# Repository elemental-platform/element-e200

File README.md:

# element-e200
Wireless motion sensor based on RFM69 radio

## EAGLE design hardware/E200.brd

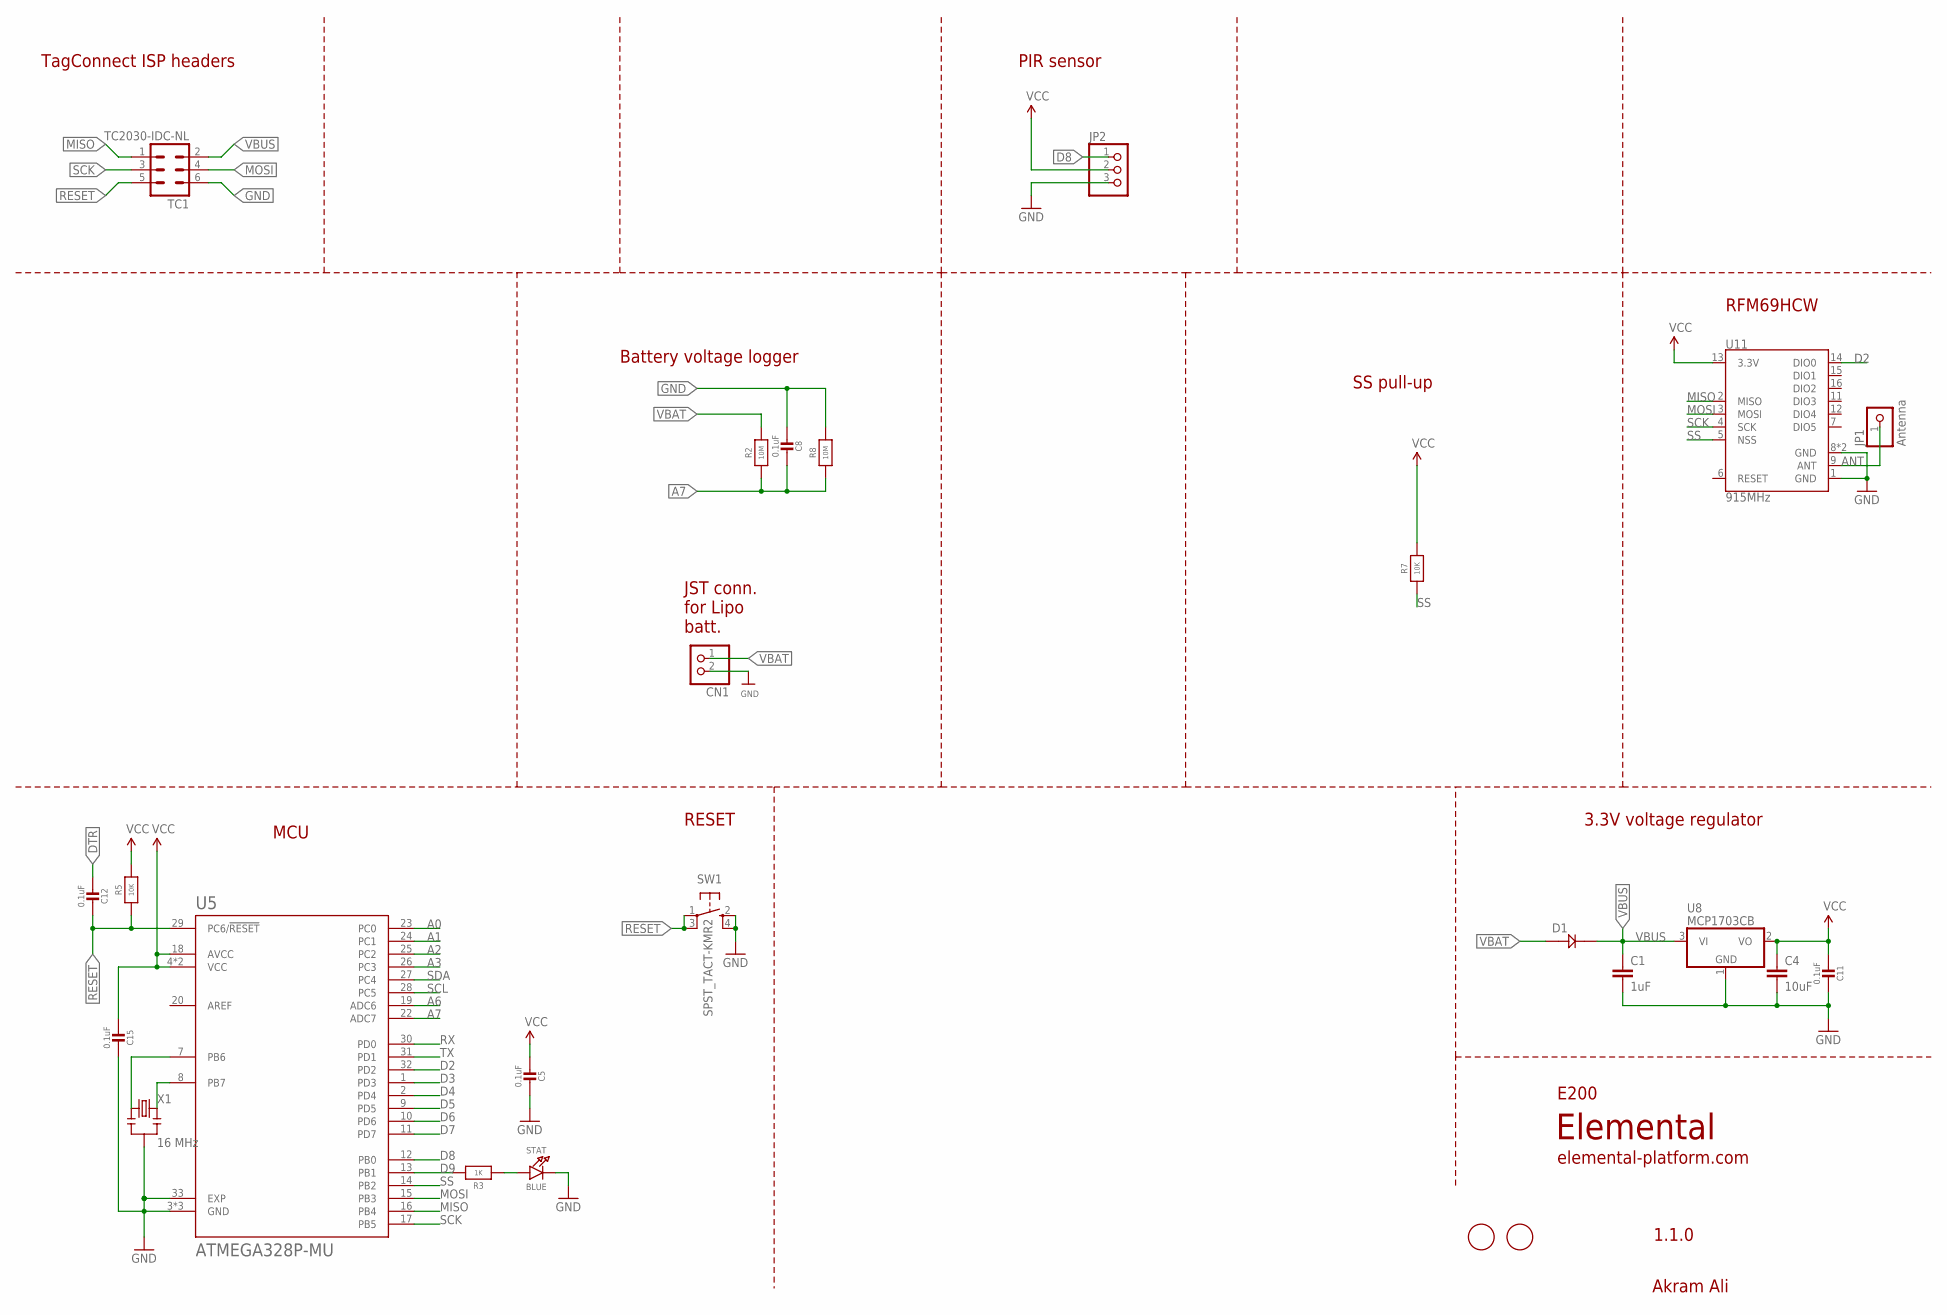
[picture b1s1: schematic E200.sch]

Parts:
C1: 1uF; 0805; MPN CC0805ZRY5V8BB105
C4: 10uF; 0805; MPN CC0805KKX5R6BB106
C5, C8, C11, C12, C15: 0.1uF; MICROBUILDER__0402MP; MPN GRM155R71C104KA88J
CN1: JST_2PIN-SMT-RA; JST-PH-2-SMT-RA
D1: DIODE_SCHOTTKY0805-RES; 0805
JP1: Antenna; 1X01-CLEANBIG; MPN Helical antenna
JP2: PINHD-1X3; 1X03
R2, R8: 10M; MICROBUILDER__0402MP; MPN RC0402JR-0710KL
R3: 1K; MICROBUILDER__0402MP; MPN RC0402JR-0710KL
R5, R7: 10K; MICROBUILDER__0402MP; MPN RC0402JR-0710KL
STAT: BLUE; CHIPLED_0805_NOOUTLINE
SW1: SPST_TACT-KMR2; KMR2
TC1: TC2030-IDC-NL
U5: ATMEGA328P-MU; QFN50P500X500X100-33N; MPN ATMEGA328P-MU
U8: MCP1703CB; SOT23; MPN MCP1703T-3302E/CB
U11: 915MHz; RFM69HCW-XXXS2; MPN RFM69HCW
U$1, U$7: FIDUCIAL; FIDUCIAL_1MM
X1: 16 MHz; RESONATOR-SMD; MPN CSTCE16M0V53-R0

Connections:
A0: U5.23 (PC0)
A1: U5.24 (PC1)
A2: U5.25 (PC2)
A3: U5.26 (PC3)
A6: U5.19 (ADC6)
A7: C8.1, R2.1, R8.1, U5.22 (ADC7)
ANT: JP1.1, U11.9 (ANT)
D2: U5.32 (PD2), U11.14 (DIO0)
D3: U5.1 (PD3)
D4: U5.2 (PD4)
D5: U5.9 (PD5)
D6: U5.10 (PD6)
D7: U5.11 (PD7)
D8: JP2.1, U5.12 (PB0)
D9: R3.2, U5.13 (PB1)
DTR: C12.2
GND: C1.2, C4.2, C5.1, C8.2, C11.1, C15.1, CN1.2 (1), JP2.3, R8.2, STAT.C, SW1.2 (S), SW1.4 (S1), TC1.6, U5.3 (GND), U5.5 (GND), U5.21 (GND), U5.33 (EXP), U8.1 (GND), U11.1 (GND), U11.8 (GND), U11.10 (GND), X1.2
MISO: TC1.1, U5.16 (PB4), U11.2 (MISO)
MOSI: TC1.4, U5.15 (PB3), U11.3 (MOSI)
unnamed: U5.8 (PB7), X1.3
unnamed: U5.7 (PB6), X1.1
unnamed: R3.1, STAT.A
RESET: C12.1, R5.1, SW1.1, SW1.3 (P1), TC1.5, U5.29 (PC6/!RESET)
RX: U5.30 (PD0)
SCK: TC1.3, U5.17 (PB5), U11.4 (SCK)
SCL: U5.28 (PC5)
SDA: U5.27 (PC4)
SS: R7.1, U5.14 (PB2), U11.5 (NSS)
TX: U5.31 (PD1)
VBAT: CN1.1 (2), D1.1, R2.2
VBUS: C1.1, D1.2, TC1.2, U8.3 (VI)
VCC: C4.1, C5.2, C11.2, C15.2, JP2.2, R5.2, R7.2, U5.4 (VCC), U5.6 (VCC), U5.18 (AVCC), U8.2 (VO), U11.13 (3.3V)

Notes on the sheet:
TagConnect ISP headers
3.3V voltage regulator
Elemental
E200
Akram Ali
1.1.0
elemental-platform.com
RFM69HCW
MCU
RESET
Battery voltage logger
JST conn. for Lipo batt.
SS pull-up
PIR sensor

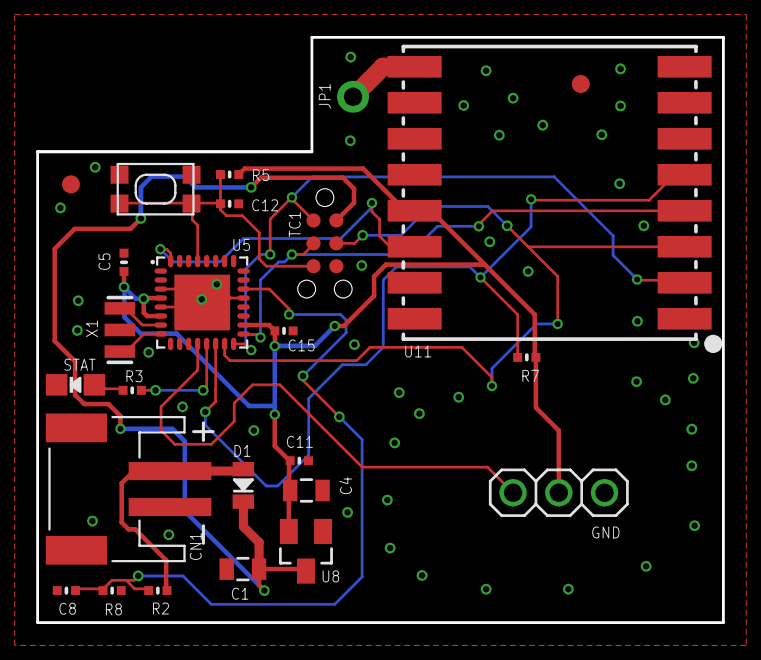
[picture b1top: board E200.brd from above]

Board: 2 copper layers, 38.1 x 32.5 mm, 25 parts (0 on the bottom side), 17 nets.

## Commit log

2019-09-02 Create LICENSE
2019-10-17 v1.1.0 - small update
    - added silkscreen to bottom for node id
    - solder mask DRU for covering vias
    - removed solder jumper
    - minor trace adjustments
    - functionally same as previous
2019-12-23 Update firmware.ino
    removed node ID from datapacket (gateway already has it in the encrypted packet, so it can retrieve it directly)
2020-01-29 change freq to 905MHz and encrypt key
    - also cleaned up the code a lot and reorganized everything properly
2020-02-05 cleaned up
    - added control node check
    - minimized some delays

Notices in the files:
parts and their libraries:
SparkFun-Capacitors: Licensing: Creative Commons ShareAlike 4.0 International - https://creativecommons.org/licenses/by-sa/4.0
microbuilder: This work is placed in the public domain, and may be freely used for commercial and non-commercial work with the following conditions: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
